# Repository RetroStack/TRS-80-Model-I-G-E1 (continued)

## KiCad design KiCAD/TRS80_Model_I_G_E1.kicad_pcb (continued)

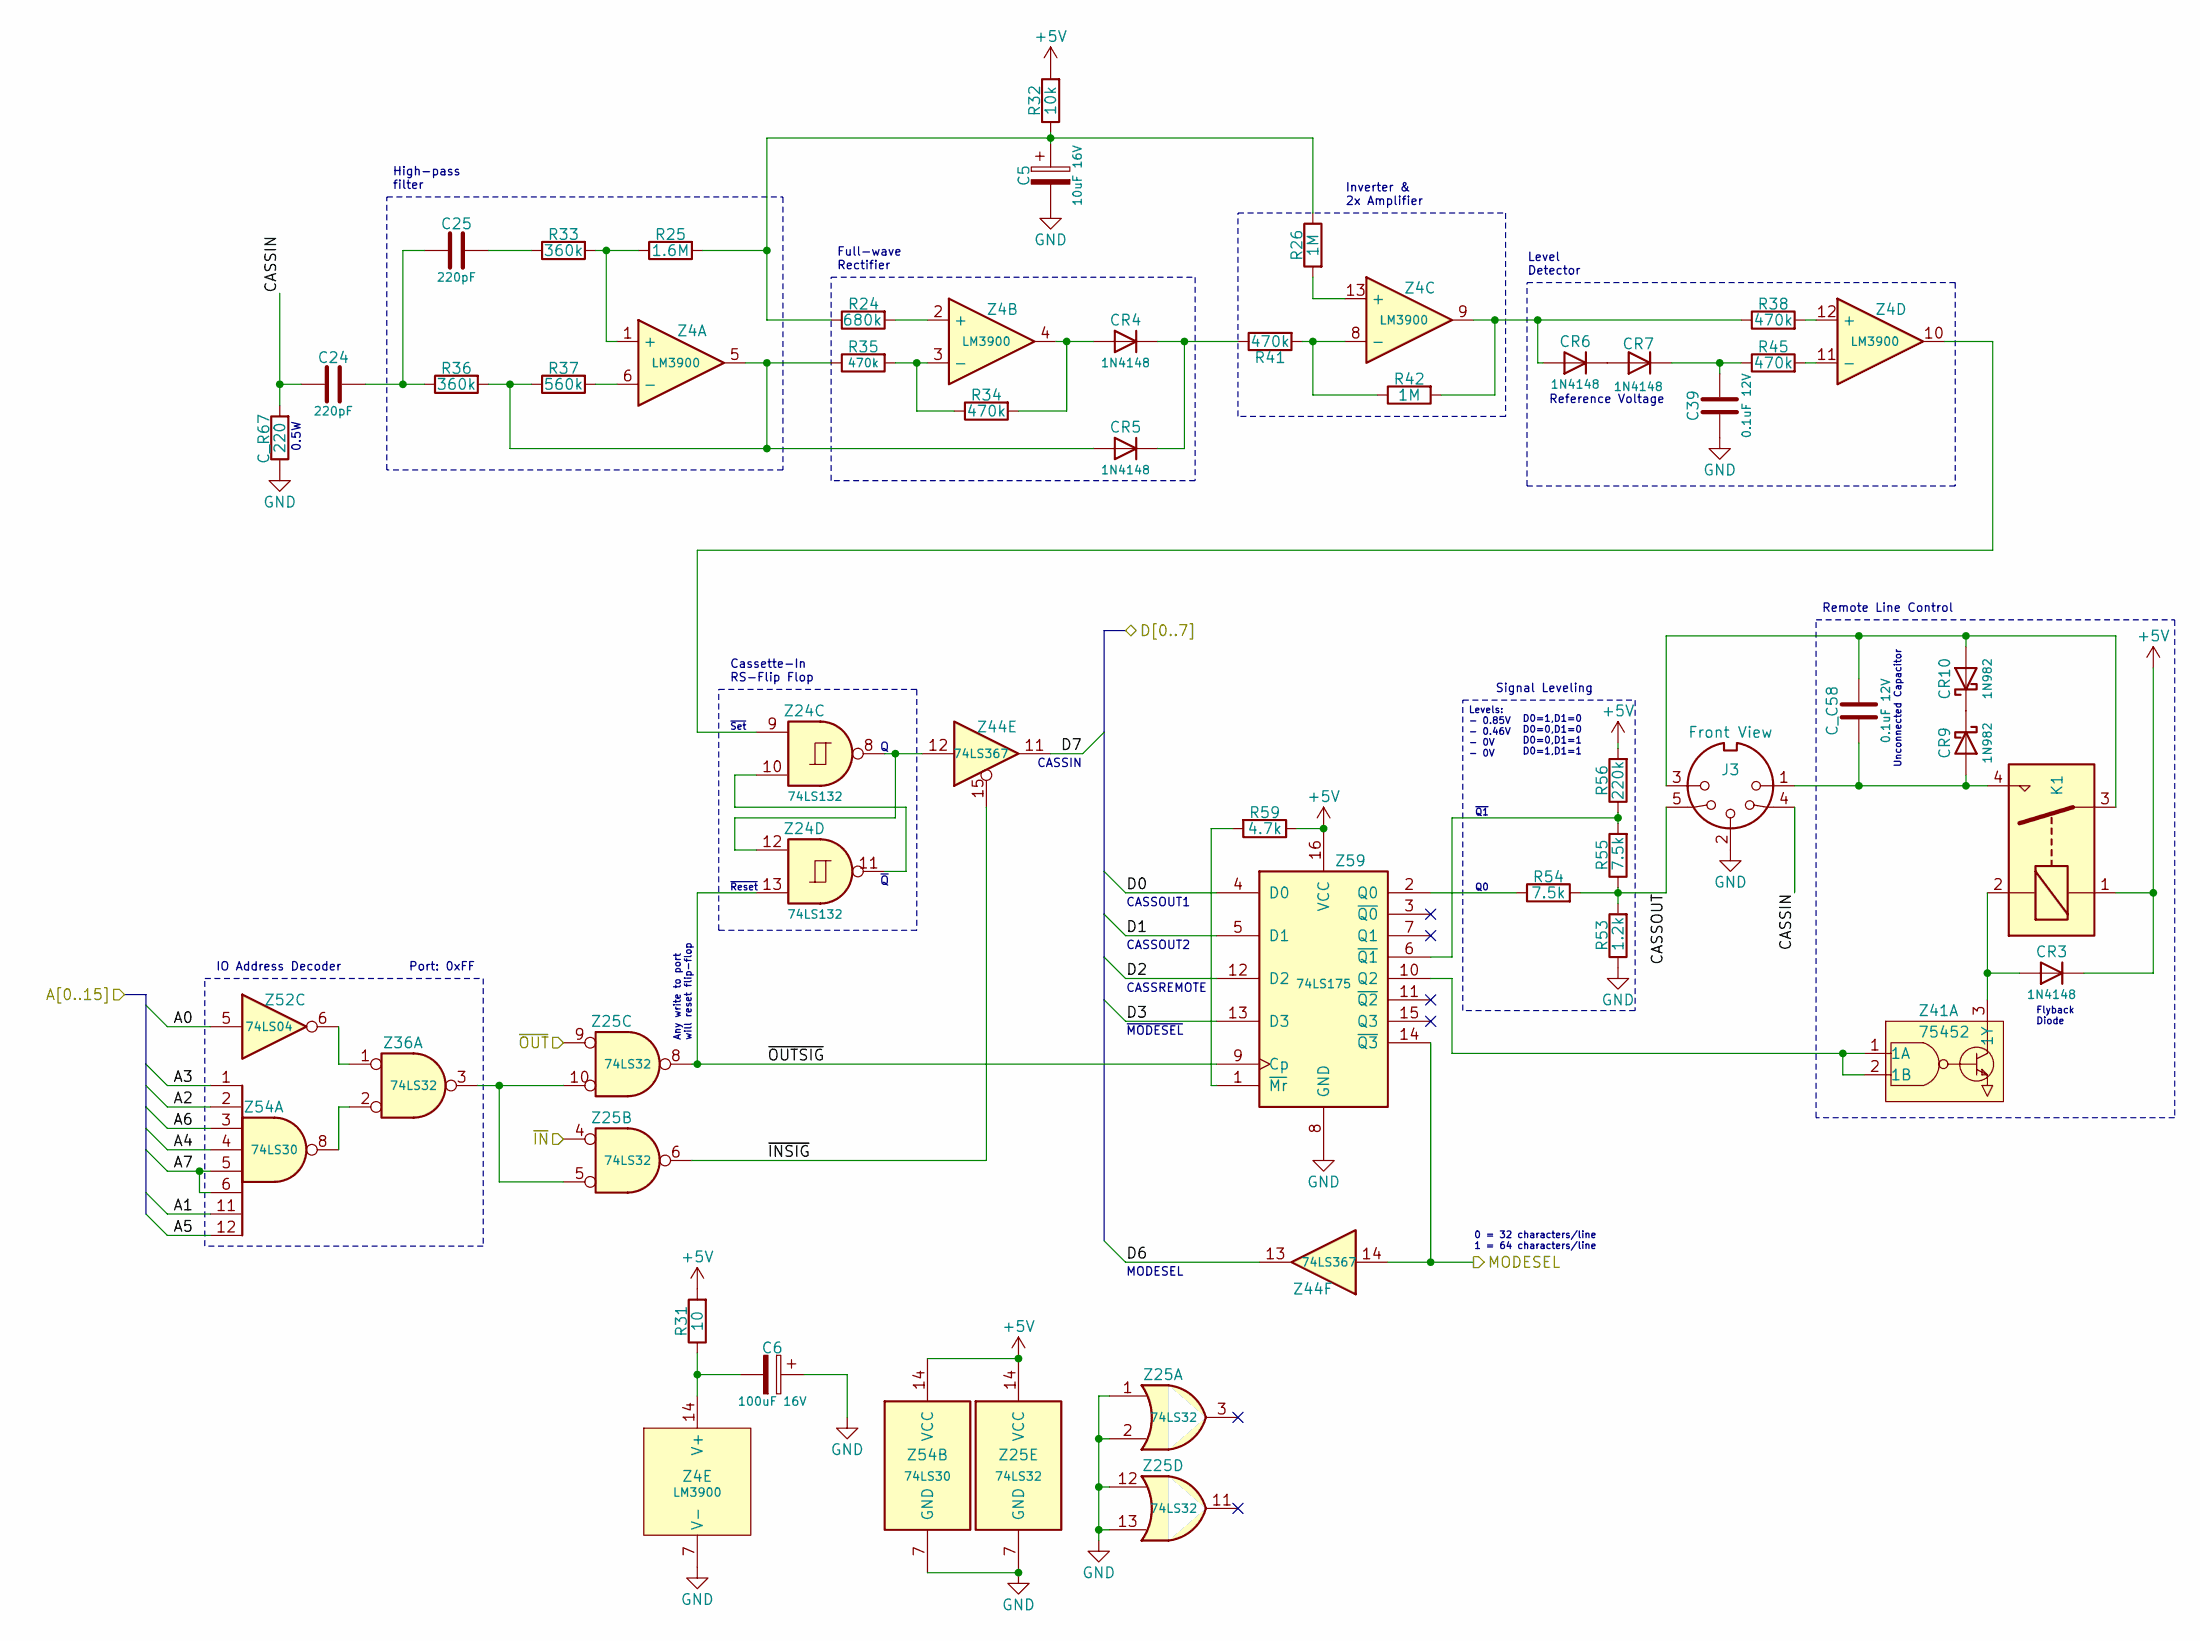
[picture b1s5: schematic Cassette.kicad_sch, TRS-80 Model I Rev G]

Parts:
C5: 10uF 16V; TRS80_Model_I_C_Pol_Radial_5D_2.5P
C6: 100uF 16V; TRS80_Model_I_C_Pol_Radial_10D_5P
C24, C25: 220pF; TRS80_Model_I_C_Disc_9.5L_4W_6P_Small
C39: 0.1uF 12V; TRS80_Model_I_C_Disc_9.5L_4W_6P_Small
CR3, CR4, CR5, CR6, CR7: 1N4148; TRS80_Model_I_D
CR9, CR10: 1N982; TRS80_Model_I_D
C_C58: 0.1uF 12V; TRS80_Model_I_C_Disc_9.5L_4W_6P_Small
C_R67: 220; TRS80_Model_I_R_0.25W
J3: Front View; TRS80_Model_I_DIN5
K1: Relay_SPST-NO; TRS80_Model_I_Relay
R24: 680k; TRS80_Model_I_R_0.25W
R25: 1.6M; TRS80_Model_I_R_0.25W
R26, R42: 1M; TRS80_Model_I_R_0.25W
R31: 10; TRS80_Model_I_R_0.25W
R32: 10k; TRS80_Model_I_R_0.25W
R33, R36: 360k; TRS80_Model_I_R_0.25W
R34, R35, R38, R41, R45: 470k; TRS80_Model_I_R_0.25W
R37: 560k; TRS80_Model_I_R_0.25W
R53: 1.2k; TRS80_Model_I_R_0.25W
R54, R55: 7.5k; TRS80_Model_I_R_0.25W
R56: 220k; TRS80_Model_I_R_0.25W
R59: 4.7k; TRS80_Model_I_R_0.25W
Z4: LM3900; TRS80_Model_I_DIP14
Z24: 74LS132; TRS80_Model_I_DIP14
Z25, Z36: 74LS32; TRS80_Model_I_DIP14
Z41: 75452; TRS80_Model_I_DIP8
Z44: 74LS367; TRS80_Model_I_DIP16
Z52: 74LS04; TRS80_Model_I_DIP14
Z54: 74LS30; TRS80_Model_I_DIP14
Z59: 74LS175; TRS80_Model_I_DIP16

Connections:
+5V: CR3.1 (K), K1.1, R31.2, R32.2, R56.2, R59.1, Z25.14 (VCC), Z54.14 (VCC), Z59.16 (VCC); also elsewhere on the board
/A0: Z52.5; also elsewhere on the board
/A1: Z54.11; also elsewhere on the board
/A2: Z54.2; also elsewhere on the board
/A3: Z54.1; also elsewhere on the board
/A4: Z54.4; also elsewhere on the board
/A5: Z54.12; also elsewhere on the board
/A6: Z54.3; also elsewhere on the board
/A7: Z54.5, Z54.6; also elsewhere on the board
/CPU Gating/~IN: Z25.4; also elsewhere on the board
/CPU Gating/~OUT: Z25.9; also elsewhere on the board
/Cassette Interface/CASSIN: C24.1, C_R67.2, J3.4
/Cassette Interface/CASSOUT: J3.5, R53.2, R54.2, R55.1
/Cassette Interface/MODESEL: Z44.14, Z59.14 (~Q3); also elsewhere on the board
/Cassette Interface/~INSIG: Z25.6, Z44.15
/Cassette Interface/~OUTSIG: Z24.13, Z25.8, Z59.9 (Cp)
/D0: Z59.4 (D0); also elsewhere on the board
/D1: Z59.5 (D1); also elsewhere on the board
/D2: Z59.12 (D2); also elsewhere on the board
/D3: Z59.13 (D3); also elsewhere on the board
/D6: Z44.13; also elsewhere on the board
/D7: Z44.11; also elsewhere on the board
GND: C5.2, C6.1, C39.1, C_R67.1, J3.2, R53.1, Z4.7 (V-), Z25.1, Z25.2, Z25.7 (GND), Z25.12, Z25.13, Z54.7 (GND), Z59.8 (GND); also elsewhere on the board
unnamed: C5.1, R24.1, R25.2, R26.1, R32.1
unnamed: C24.2, C25.1, R36.1
unnamed: C25.2, R33.1
unnamed: CR3.2 (A), K1.2, Z41.3 (1Y)
unnamed: CR4.2 (A), R34.2, Z4.4
unnamed: CR4.1 (K), CR5.1 (K), R41.1
unnamed: CR5.2 (A), R35.1, R36.2, R37.1, Z4.5
unnamed: CR6.2 (A), R38.1, R42.2, Z4.9
unnamed: CR6.1 (K), CR7.2 (A)
unnamed: C39.2, CR7.1 (K), R45.1
unnamed: CR9.2 (A), C_C58.2, J3.1, K1.4
unnamed: CR10.2 (A), C_C58.1, J3.3, K1.3
unnamed: CR9.1 (K), CR10.1 (K)
unnamed: R25.1, R33.2, Z4.1 (+)
unnamed: R37.2, Z4.6 (-)
unnamed: R24.2, Z4.2 (+)
unnamed: R34.1, R35.2, Z4.3 (-)
unnamed: R26.2, Z4.13 (+)
unnamed: R41.2, R42.1, Z4.8 (-)
unnamed: R38.2, Z4.12 (+)
unnamed: R45.2, Z4.11 (-)
unnamed: C6.2, R31.1, Z4.14 (V+)
unnamed: Z4.10, Z24.9
unnamed: Z24.10, Z24.11
unnamed: Z24.8, Z24.12, Z44.12
unnamed: Z25.5, Z25.10, Z36.3
unnamed: Z36.1, Z52.6
unnamed: Z36.2, Z54.8
unnamed: Z41.1 (1A), Z41.2 (1B), Z59.10 (Q2)
unnamed: R54.1, Z59.2 (Q0)
unnamed: R59.2, Z59.1 (~Mr)
unnamed: R55.2, R56.1, Z59.6 (~Q1)

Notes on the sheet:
~{MODESEL}
0 = 32 characters/line 1 = 64 characters/line
Full-wave Rectifier
Level Detector
High-pass filter
Unconnected Capacitor
Reference Voltage
Any write to port will reset flip-flop
IO Address Decoder
CASSREMOTE
Remote Line Control
Port: 0xFF
~{Q}
CASSOUT1
Flyback Diode
Signal Leveling
0.5W
CASSOUT2
CASSIN
MODESEL
Cassette-In RS-Flip Flop
~{Q1}
Levels: - 0.85V - 0.46V - 0V - 0V
Inverter & 2x Amplifier
~{Reset}
~{Set}
D0=1,D1=0 D0=0,D1=0 D0=0,D1=1 D0=1,D1=1

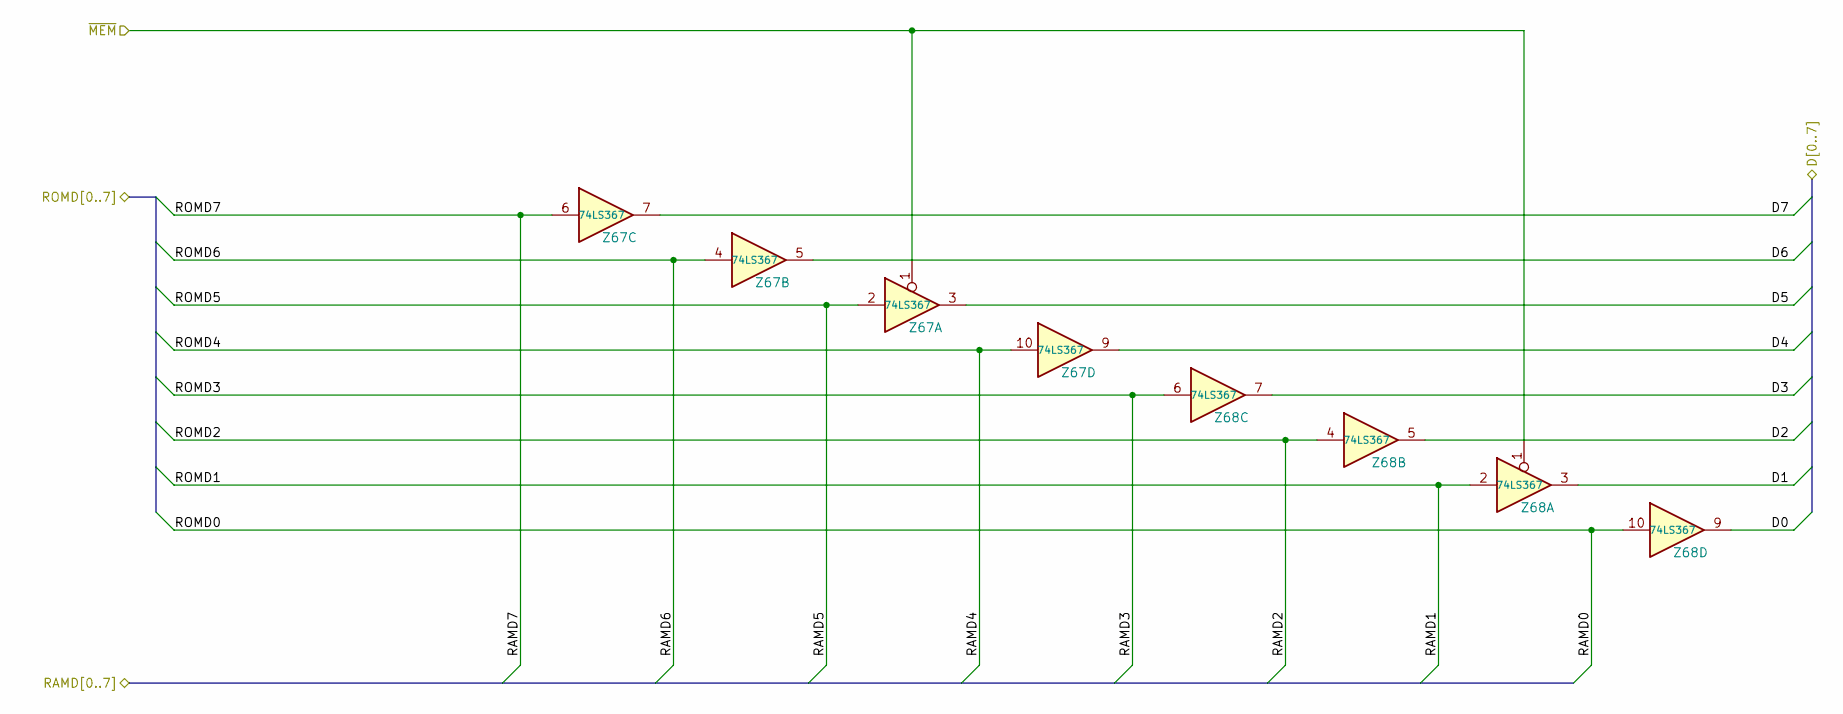
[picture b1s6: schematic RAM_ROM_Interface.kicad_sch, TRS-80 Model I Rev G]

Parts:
Z67, Z68: 74LS367; TRS80_Model_I_DIP16

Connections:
/Address Decoder/~MEM: Z67.1, Z68.1; also elsewhere on the board
/D0: Z68.9; also elsewhere on the board
/D1: Z68.3; also elsewhere on the board
/D2: Z68.5; also elsewhere on the board
/D3: Z68.7; also elsewhere on the board
/D4: Z67.9; also elsewhere on the board
/D5: Z67.3; also elsewhere on the board
/D6: Z67.5; also elsewhere on the board
/D7: Z67.7; also elsewhere on the board
/RAM-ROM Interface/ROMD0: Z68.10; also elsewhere on the board
/RAM-ROM Interface/ROMD1: Z68.2; also elsewhere on the board
/RAM-ROM Interface/ROMD2: Z68.4; also elsewhere on the board
/RAM-ROM Interface/ROMD3: Z68.6; also elsewhere on the board
/RAM-ROM Interface/ROMD4: Z67.10; also elsewhere on the board
/RAM-ROM Interface/ROMD5: Z67.2; also elsewhere on the board
/RAM-ROM Interface/ROMD6: Z67.4; also elsewhere on the board
/RAM-ROM Interface/ROMD7: Z67.6; also elsewhere on the board

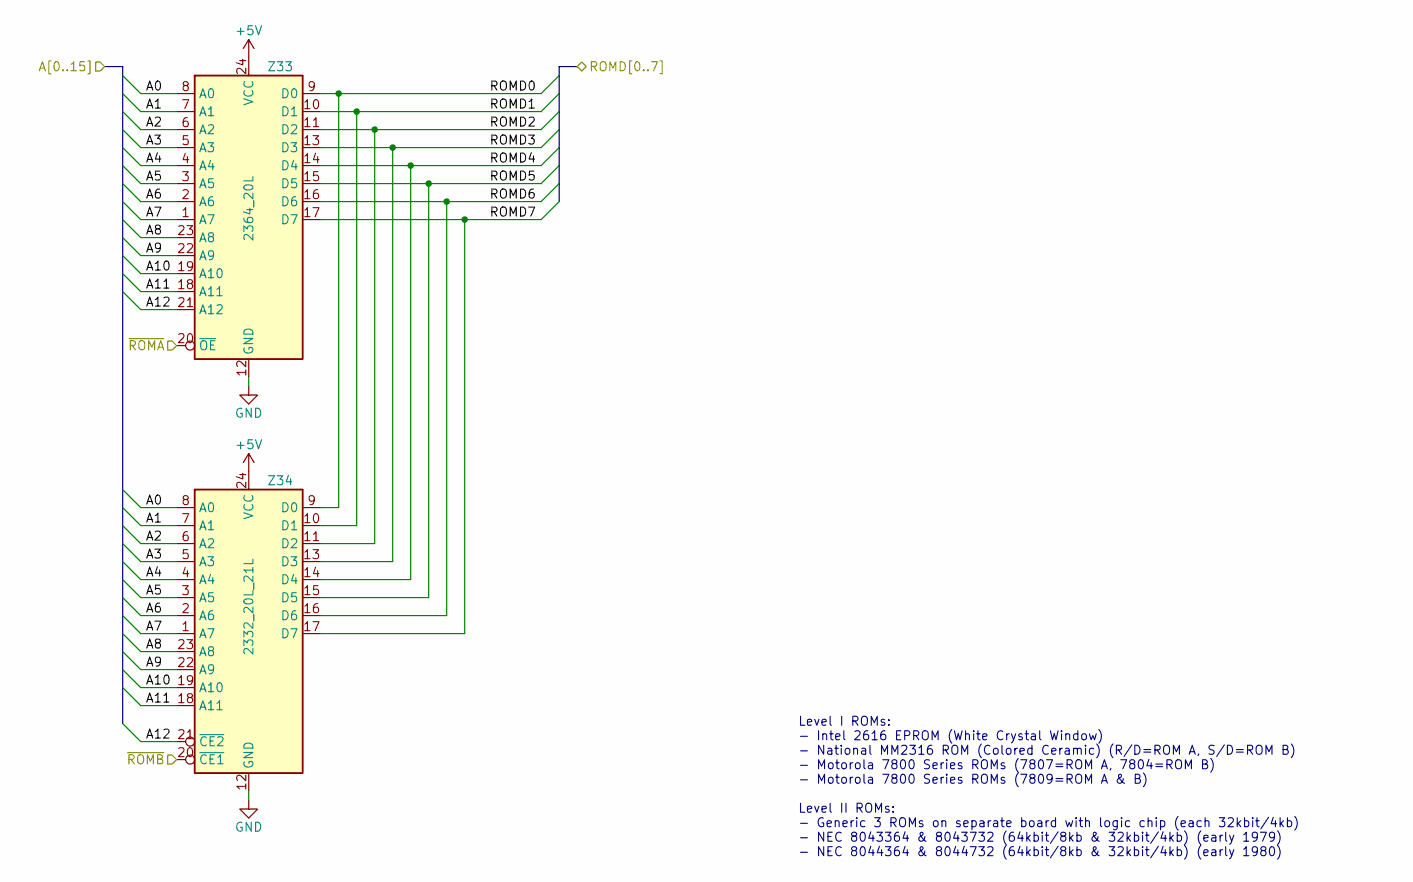
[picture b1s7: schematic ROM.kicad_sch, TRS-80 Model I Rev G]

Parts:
Z33: 2364_20L; DIP-24_W15.24mm
Z34: 2332_20L_21L; DIP-24_W15.24mm

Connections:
+5V: Z33.24 (VCC), Z34.24 (VCC); also elsewhere on the board
/A0: Z33.8 (A0), Z34.8 (A0); also elsewhere on the board
/A1: Z33.7 (A1), Z34.7 (A1); also elsewhere on the board
/A2: Z33.6 (A2), Z34.6 (A2); also elsewhere on the board
/A3: Z33.5 (A3), Z34.5 (A3); also elsewhere on the board
/A4: Z33.4 (A4), Z34.4 (A4); also elsewhere on the board
/A5: Z33.3 (A5), Z34.3 (A5); also elsewhere on the board
/A6: Z33.2 (A6), Z34.2 (A6); also elsewhere on the board
/A7: Z33.1 (A7), Z34.1 (A7); also elsewhere on the board
/A8: Z33.23 (A8), Z34.23 (A8); also elsewhere on the board
/A9: Z33.22 (A9), Z34.22 (A9); also elsewhere on the board
/A10: Z33.19 (A10), Z34.19 (A10); also elsewhere on the board
/A11: Z33.18 (A11), Z34.18 (A11); also elsewhere on the board
/A12: Z33.21 (A12), Z34.21 (~CE2); also elsewhere on the board
/Address Decoder/~ROMA: Z33.20 (~OE); also elsewhere on the board
/Address Decoder/~ROMB: Z34.20 (~CE1); also elsewhere on the board
/RAM-ROM Interface/ROMD0: Z33.9 (D0), Z34.9 (D0); also elsewhere on the board
/RAM-ROM Interface/ROMD1: Z33.10 (D1), Z34.10 (D1); also elsewhere on the board
/RAM-ROM Interface/ROMD2: Z33.11 (D2), Z34.11 (D2); also elsewhere on the board
/RAM-ROM Interface/ROMD3: Z33.13 (D3), Z34.13 (D3); also elsewhere on the board
/RAM-ROM Interface/ROMD4: Z33.14 (D4), Z34.14 (D4); also elsewhere on the board
/RAM-ROM Interface/ROMD5: Z33.15 (D5), Z34.15 (D5); also elsewhere on the board
/RAM-ROM Interface/ROMD6: Z33.16 (D6), Z34.16 (D6); also elsewhere on the board
/RAM-ROM Interface/ROMD7: Z33.17 (D7), Z34.17 (D7); also elsewhere on the board
GND: Z33.12 (GND), Z34.12 (GND); also elsewhere on the board

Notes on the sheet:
Level I ROMs: - Intel 2616 EPROM (White Crystal Window) - National MM2316 ROM (Colored Ceramic) (R/D=ROM A, S/D=ROM B) - Motorola 7800 Series ROMs (7807=ROM A, 7804=ROM B) - Motorola 7800 Series ROMs (7809=ROM A & B) Level II ROMs: - Generic 3 ROMs on separate board with logic chip (each 32kbit/4kb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

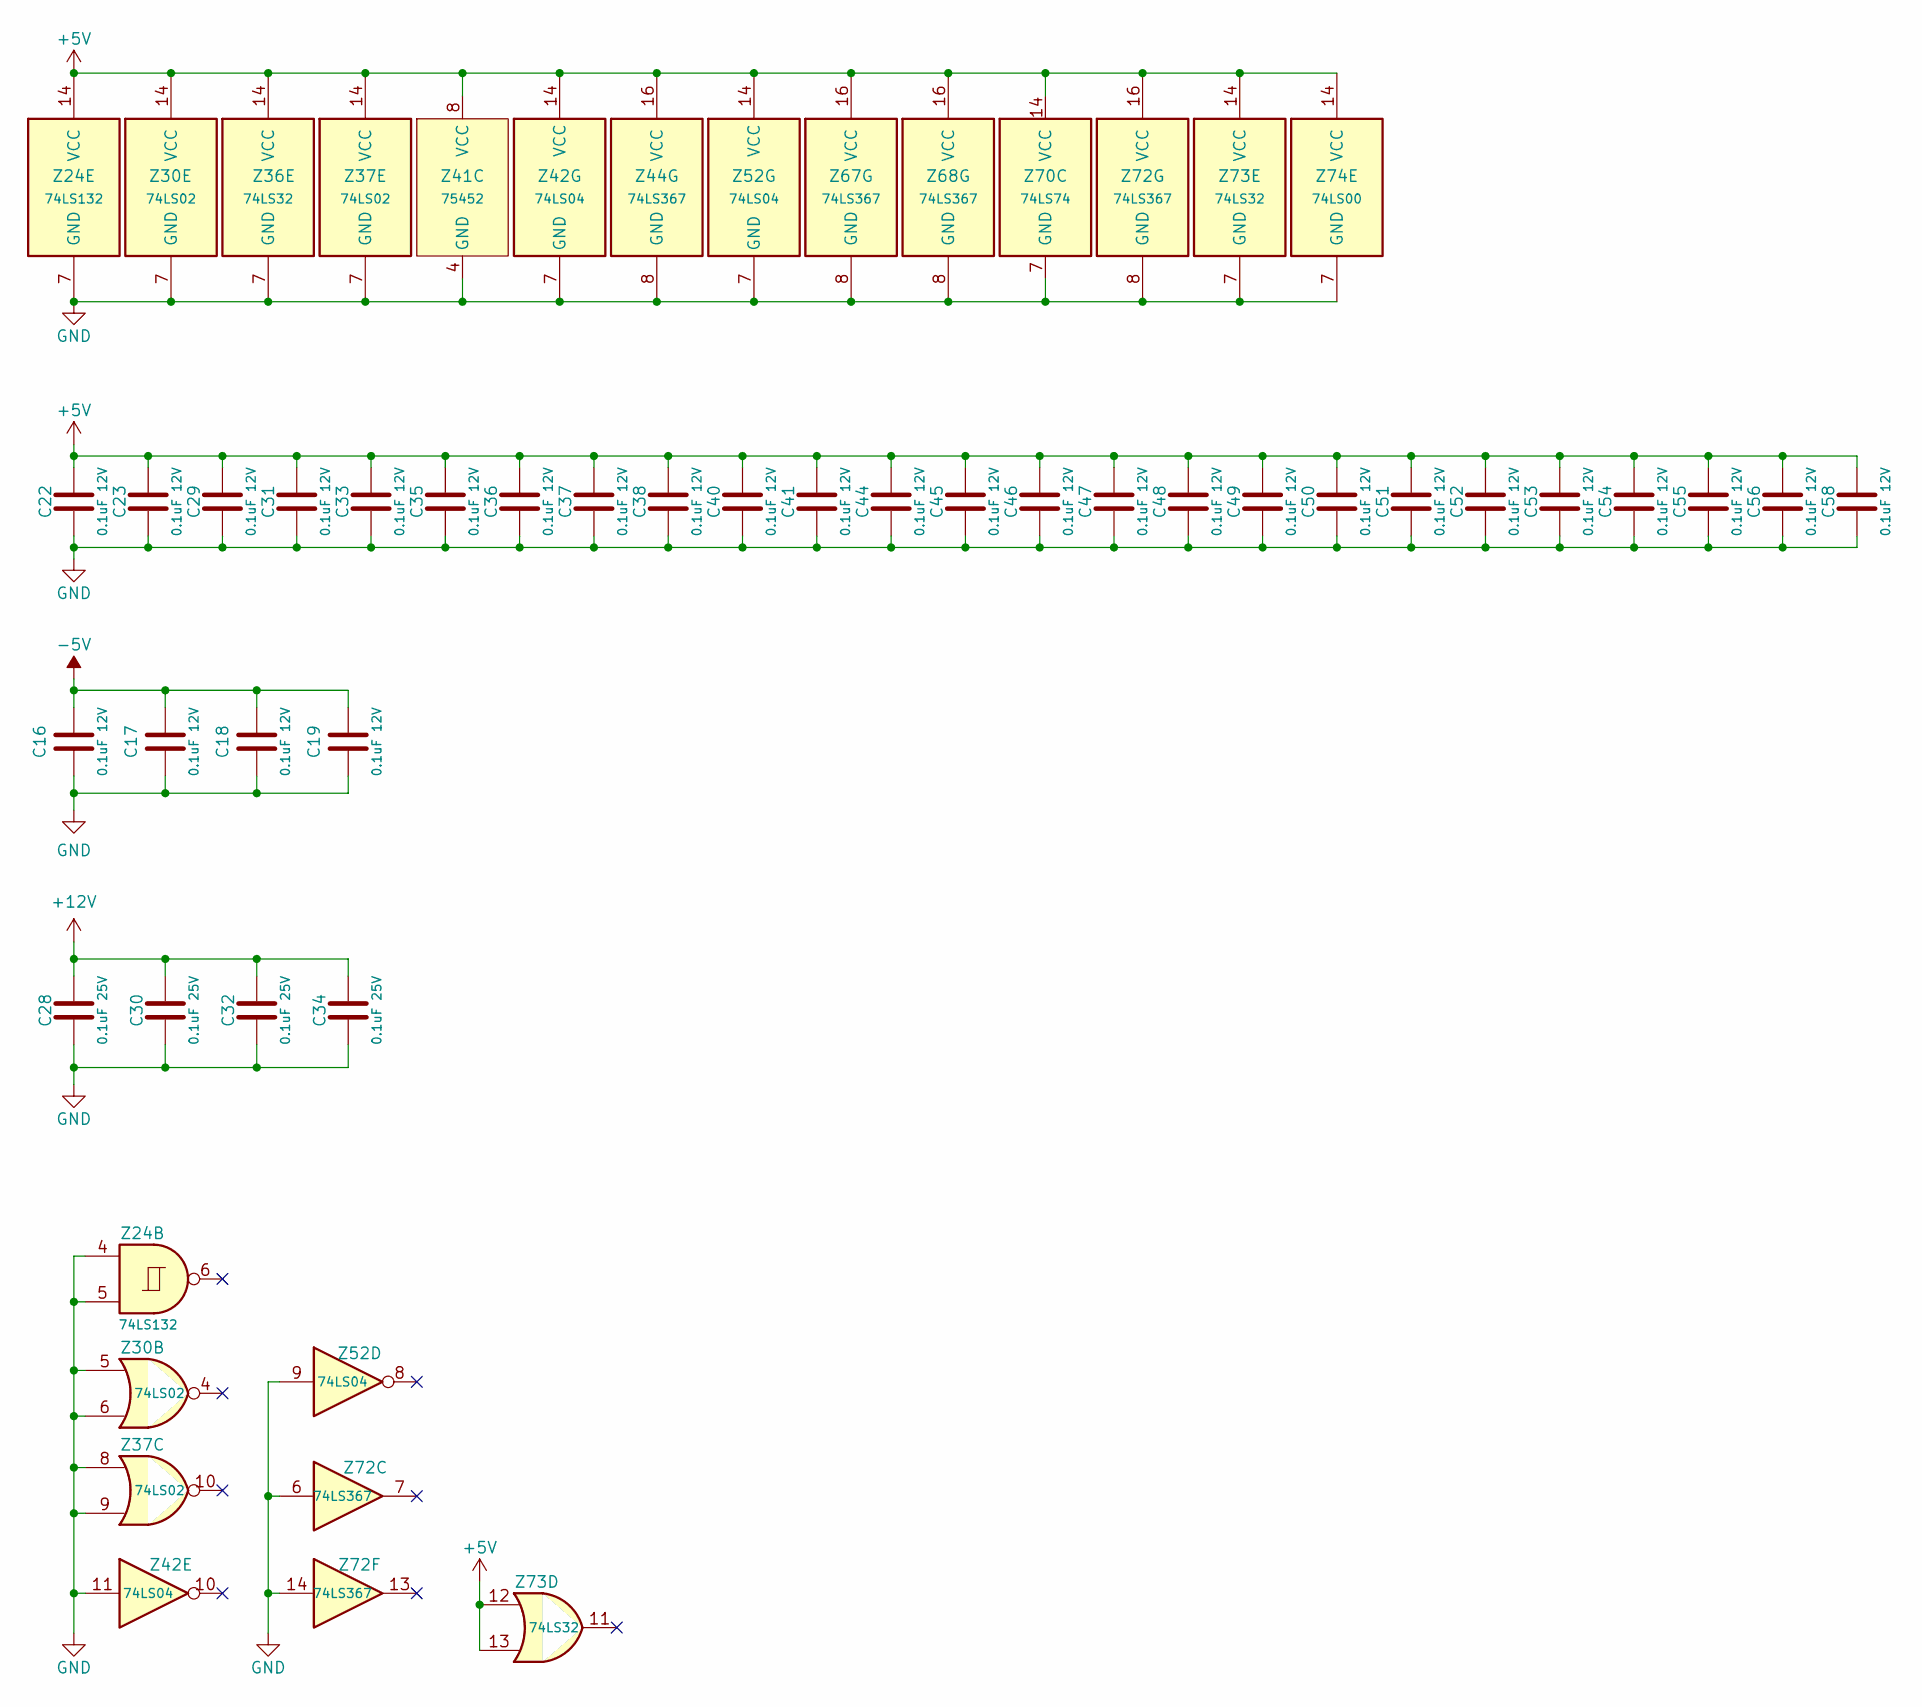
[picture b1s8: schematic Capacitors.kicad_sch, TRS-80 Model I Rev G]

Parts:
C16, C17, C18, C19, C22, C23, C29, C31, C33, C35, C36, C37, C38, C40, C41, C44, C45, C46, C47, C48, C49, C50, C51, C52, C53, C54, C55, C56, C58: 0.1uF 12V; TRS80_Model_I_C_Disc_9.5L_4W_6P_Small
C28, C30, C32, C34: 0.1uF 25V; TRS80_Model_I_C_Disc_18.5L_4W_8.5P_Large
Z24: 74LS132; TRS80_Model_I_DIP14
Z30, Z37: 74LS02; TRS80_Model_I_DIP14
Z36, Z73: 74LS32; TRS80_Model_I_DIP14
Z41: 75452; TRS80_Model_I_DIP8
Z42, Z52: 74LS04; TRS80_Model_I_DIP14
Z44, Z67, Z68, Z72: 74LS367; TRS80_Model_I_DIP16
Z70: 74LS74; TRS80_Model_I_DIP14
Z74: 74LS00; TRS80_Model_I_DIP14

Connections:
+5V: C22.1, C23.1, C29.1, C31.1, C33.1, C35.1, C36.1, C37.1, C38.1, C40.1, C41.1, C44.1, C45.1, C46.1, C47.1, C48.1, C49.1, C50.1, C51.1, C52.1, C53.1, C54.1, C55.1, C56.1, C58.1, Z24.14 (VCC), Z30.14 (VCC), Z36.14 (VCC), Z37.14 (VCC), Z41.8 (VCC), Z42.14 (VCC), Z44.16 (VCC), Z52.14 (VCC), Z67.16 (VCC), Z68.16 (VCC), Z70.14 (VCC), Z72.16 (VCC), Z73.12, Z73.13, Z73.14 (VCC), Z74.14 (VCC); also elsewhere on the board
+12V: C28.1, C30.1, C32.1, C34.1; also elsewhere on the board
-5V: C16.1, C17.1, C18.1, C19.1; also elsewhere on the board
/Cassette Interface/MODESEL: Z44.14; also elsewhere on the board
/D6: Z44.13; also elsewhere on the board
GND: C16.2, C17.2, C18.2, C19.2, C22.2, C23.2, C28.2, C29.2, C30.2, C31.2, C32.2, C33.2, C34.2, C35.2, C36.2, C37.2, C38.2, C40.2, C41.2, C44.2, C45.2, C46.2, C47.2, C48.2, C49.2, C50.2, C51.2, C52.2, C53.2, C54.2, C55.2, C56.2, C58.2, Z24.4, Z24.5, Z24.7 (GND), Z30.5, Z30.6, Z30.7 (GND), Z36.7 (GND), Z37.7 (GND), Z37.8, Z37.9, Z41.4 (GND), Z42.7 (GND), Z42.11, Z44.8 (GND), Z52.7 (GND), Z52.9, Z67.8 (GND), Z68.8 (GND), Z70.7 (GND), Z72.6, Z72.8 (GND), Z72.14, Z73.7 (GND), Z74.7 (GND); also elsewhere on the board

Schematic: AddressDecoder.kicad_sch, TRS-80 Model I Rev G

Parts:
R48, R61, R62, R68: 4.7k; TRS80_Model_I_R_0.25W
Z3: DIP-16_W7.62mm
Z21: 74LS156; TRS80_Model_I_DIP16
Z36, Z73: 74LS32; TRS80_Model_I_DIP14
Z37: 74LS02; TRS80_Model_I_DIP14
Z52: 74LS04; TRS80_Model_I_DIP14
Z74: 74LS00; TRS80_Model_I_DIP14

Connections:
+5V: R48.2, R61.2, R62.2, R68.2, Z21.16 (VCC); also elsewhere on the board
/A10: Z36.13, Z52.1; also elsewhere on the board
/A11: Z37.5, Z37.6; also elsewhere on the board
/A12: Z21.13 (A0); also elsewhere on the board
/A13: Z21.3 (A1); also elsewhere on the board
/A14: Z21.1 (Ea1), Z21.15 (Eb2); also elsewhere on the board
/A15: Z73.4; also elsewhere on the board
/Address Decoder/~KYBD: Z36.11; also elsewhere on the board
/Address Decoder/~MEM: Z74.6; also elsewhere on the board
/Address Decoder/~RAM: R62.1, Z3.12, Z3.13, Z3.14, Z3.15, Z74.10; also elsewhere on the board
/Address Decoder/~RAS: Z73.5; also elsewhere on the board
/Address Decoder/~RD: Z52.13; also elsewhere on the board
/Address Decoder/~ROMA: R61.1, Z3.7, Z3.8, Z74.9; also elsewhere on the board
/Address Decoder/~ROMB: R68.1, Z3.1, Z3.6, Z74.12, Z74.13; also elsewhere on the board
/Address Decoder/~VID: Z36.8; also elsewhere on the board
GND: Z21.8 (GND); also elsewhere on the board
unnamed: Z21.2 (Ea2), Z21.14 (Eb1), Z73.6
unnamed: Z3.2, Z21.7 (Q0a)
unnamed: Z3.10, Z3.16, Z21.9 (Q0b)
unnamed: Z3.3, Z21.6 (Q1a)
unnamed: Z3.9, Z21.10 (Q1b)
unnamed: Z3.4, Z21.5 (Q2a)
unnamed: Z3.11, Z21.11 (Q2b)
unnamed: Z3.5, Z21.4 (Q3a)
unnamed: R48.1, Z21.12 (Q3b), Z36.4
unnamed: Z36.5, Z37.4
unnamed: Z36.9, Z52.2
unnamed: Z36.6, Z36.10, Z36.12
unnamed: Z52.12, Z74.4
unnamed: Z73.8, Z74.5
unnamed: Z73.9, Z74.8
unnamed: Z73.10, Z74.11

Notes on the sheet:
38xx..3Bxx
5xxx
4xxx
0001
0000
0111
RAS=0 && A15=0
7xxx
0xxx, 2xxx
2xxx
0100
0xxx, 1xxx
0011
4xxx..7xxx
0010
0101
3Cxx..3Fxx
0xxx
A14=0
A14=1
0110
6xxx
1xxx
3xxx

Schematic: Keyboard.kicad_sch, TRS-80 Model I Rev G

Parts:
J100: Connection Mainboard Side; TRS80_Model_I_Keyboard_Connector

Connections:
+5V: J100.1; also elsewhere on the board
/A0: J100.5; also elsewhere on the board
/A1: J100.4; also elsewhere on the board
/A2: J100.6; also elsewhere on the board
/A3: J100.9; also elsewhere on the board
/A4: J100.2; also elsewhere on the board
/A5: J100.3; also elsewhere on the board
/A6: J100.7; also elsewhere on the board
/A7: J100.8; also elsewhere on the board
/Address Decoder/~KYBD: J100.14; also elsewhere on the board
/D0: J100.11; also elsewhere on the board
/D1: J100.16; also elsewhere on the board
/D2: J100.10; also elsewhere on the board
/D3: J100.13; also elsewhere on the board
/D4: J100.18; also elsewhere on the board
/D5: J100.12; also elsewhere on the board
/D6: J100.15; also elsewhere on the board
/D7: J100.17; also elsewhere on the board
GND: J100.19; also elsewhere on the board

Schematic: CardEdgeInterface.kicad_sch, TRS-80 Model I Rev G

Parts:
J4: Edge Connector; TRS80_Model_I_Edge_Connector
R50, R51, R58: 4.7k; TRS80_Model_I_R_0.25W

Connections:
+5V: R50.1, R51.1, R58.1; also elsewhere on the board
/A0: J4.25; also elsewhere on the board
/A1: J4.27; also elsewhere on the board
/A2: J4.40; also elsewhere on the board
/A3: J4.34; also elsewhere on the board
/A4: J4.31; also elsewhere on the board
/A5: J4.35; also elsewhere on the board
/A6: J4.38; also elsewhere on the board
/A7: J4.36; also elsewhere on the board
/A8: J4.11; also elsewhere on the board
/A9: J4.17; also elsewhere on the board
/A10: J4.4; also elsewhere on the board
/A11: J4.9; also elsewhere on the board
/A12: J4.5; also elsewhere on the board
/A13: J4.6; also elsewhere on the board
/A14: J4.10; also elsewhere on the board
/A15: J4.7; also elsewhere on the board
/Address Decoder/~RAS: J4.1; also elsewhere on the board
/Address Decoder/~RD: J4.15; also elsewhere on the board
/CPU Gating/MUX: J4.16; also elsewhere on the board
/CPU Gating/~CAS: J4.3; also elsewhere on the board
/CPU Gating/~IN: J4.19; also elsewhere on the board
/CPU Gating/~OUT: J4.12; also elsewhere on the board
/CPU Gating/~TEST: J4.23, R58.2; also elsewhere on the board
/CPU Gating/~WR: J4.13; also elsewhere on the board
/CPU/~INTAK: J4.14; also elsewhere on the board
/CPU/~INT: J4.21, R50.2; also elsewhere on the board
/CPU/~SYSRES: J4.2; also elsewhere on the board
/CPU/~WAIT: J4.33, R51.2; also elsewhere on the board
/D0: J4.30; also elsewhere on the board
/D1: J4.22; also elsewhere on the board
/D2: J4.32; also elsewhere on the board
/D3: J4.26; also elsewhere on the board
/D4: J4.18; also elsewhere on the board
/D5: J4.28; also elsewhere on the board
/D6: J4.24; also elsewhere on the board
/D7: J4.20; also elsewhere on the board
GND: J4.8, J4.29, J4.37, J4.39; also elsewhere on the board

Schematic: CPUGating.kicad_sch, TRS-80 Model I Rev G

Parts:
Z22, Z38, Z39, Z55, Z72, Z75, Z76: 74LS367; TRS80_Model_I_DIP16
Z52: 74LS04; TRS80_Model_I_DIP14

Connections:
+5V: Z22.16 (VCC), Z38.16 (VCC), Z39.16 (VCC), Z55.16 (VCC), Z75.16 (VCC), Z76.16 (VCC); also elsewhere on the board
/A0: Z55.11; also elsewhere on the board
/A1: Z55.13; also elsewhere on the board
/A2: Z22.11; also elsewhere on the board
/A3: Z22.13; also elsewhere on the board
/A4: Z39.7; also elsewhere on the board
/A5: Z39.9; also elsewhere on the board
/A6: Z39.5; also elsewhere on the board
/A7: Z39.11; also elsewhere on the board
/A8: Z39.3; also elsewhere on the board
/A9: Z39.13; also elsewhere on the board
/A10: Z38.3; also elsewhere on the board
/A11: Z38.13; also elsewhere on the board
/A12: Z38.5; also elsewhere on the board
/A13: Z38.7; also elsewhere on the board
/A14: Z38.11; also elsewhere on the board
/A15: Z38.9; also elsewhere on the board
/Address Decoder/~RAS: Z72.5; also elsewhere on the board
/Address Decoder/~RD: Z22.7; also elsewhere on the board
/CPU Gating/MUX: Z72.3; also elsewhere on the board
/CPU Gating/ZA0: Z55.12; also elsewhere on the board
/CPU Gating/ZA1: Z55.14; also elsewhere on the board
/CPU Gating/ZA2: Z22.12; also elsewhere on the board
/CPU Gating/ZA3: Z22.14; also elsewhere on the board
/CPU Gating/ZA4: Z39.6; also elsewhere on the board
/CPU Gating/ZA5: Z39.10; also elsewhere on the board
/CPU Gating/ZA6: Z39.4; also elsewhere on the board
/CPU Gating/ZA7: Z39.12; also elsewhere on the board
/CPU Gating/ZA8: Z39.2; also elsewhere on the board
/CPU Gating/ZA9: Z39.14; also elsewhere on the board
/CPU Gating/ZA10: Z38.2; also elsewhere on the board
/CPU Gating/ZA11: Z38.14; also elsewhere on the board
/CPU Gating/ZA12: Z38.4; also elsewhere on the board
/CPU Gating/ZA13: Z38.6; also elsewhere on the board
/CPU Gating/ZA14: Z38.12; also elsewhere on the board
/CPU Gating/ZA15: Z38.10; also elsewhere on the board
/CPU Gating/ZD0: Z76.9, Z76.12; also elsewhere on the board
/CPU Gating/ZD1: Z76.3, Z76.14; also elsewhere on the board
/CPU Gating/ZD2: Z75.14, Z76.5; also elsewhere on the board
/CPU Gating/ZD3: Z55.5, Z75.4; also elsewhere on the board
/CPU Gating/ZD4: Z55.3, Z75.6; also elsewhere on the board
/CPU Gating/ZD5: Z55.7, Z75.2; also elsewhere on the board
/CPU Gating/ZD6: Z55.9, Z75.10; also elsewhere on the board
/CPU Gating/ZD7: Z75.12, Z76.7; also elsewhere on the board
/CPU Gating/ZMUX: Z72.2; also elsewhere on the board
/CPU Gating/~CAS: Z72.9; also elsewhere on the board
/CPU Gating/~DBIN: Z55.1, Z76.1; also elsewhere on the board
/CPU Gating/~DBOUT: Z75.1, Z75.15, Z76.15; also elsewhere on the board
/CPU Gating/~IN: Z22.9; also elsewhere on the board
/CPU Gating/~OUT: Z22.3; also elsewhere on the board
/CPU Gating/~TEST: Z52.3; also elsewhere on the board
/CPU Gating/~WR: Z22.5; also elsewhere on the board
/CPU Gating/~ZCAS: Z72.10; also elsewhere on the board
/CPU Gating/~ZIN: Z22.10; also elsewhere on the board
/CPU Gating/~ZOUT: Z22.2; also elsewhere on the board
/CPU Gating/~ZRAS: Z72.4; also elsewhere on the board
/CPU Gating/~ZRD: Z22.6; also elsewhere on the board
/CPU Gating/~ZWR: Z22.4; also elsewhere on the board
/D0: Z76.10, Z76.11; also elsewhere on the board
/D1: Z76.2, Z76.13; also elsewhere on the board
/D2: Z75.13, Z76.4; also elsewhere on the board
/D3: Z55.4, Z75.5; also elsewhere on the board
/D4: Z55.2, Z75.7; also elsewhere on the board
/D5: Z55.6, Z75.3; also elsewhere on the board
/D6: Z55.10, Z75.9; also elsewhere on the board
/D7: Z75.11, Z76.6; also elsewhere on the board
GND: Z22.8 (GND), Z38.8 (GND), Z39.8 (GND), Z55.8 (GND), Z75.8 (GND), Z76.8 (GND); also elsewhere on the board
unnamed: Z22.1, Z22.15, Z38.1, Z38.15, Z39.1, Z39.15, Z52.4, Z55.15, Z72.1

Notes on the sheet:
Bi-directional Data Bus
Address Bus
Control Signals

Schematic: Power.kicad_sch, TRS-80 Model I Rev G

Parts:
C1: 220uF 16V; TRS80_Model_I_C_Pol_Axial_21L_9W_29P
C3, C14, C15: 0.01uF 24V; TRS80_Model_I_C_Disc_9.5L_4W_6P_Small
C4, C10, C11: 10uF 16V; TRS80_Model_I_C_Pol_Radial_5D_2.5P
C8: 2200uF 35V; TRS80_Model_I_C_Pol_Axial_41L_19W_48P
C9: 10000uF 16V; TRS80_Model_I_C_Pol_Axial_63L_25W_71P
C12, C13: 470pF; TRS80_Model_I_C_Disc_9.5L_4W_6P_Small
CR1: 1N4735; TRS80_Model_I_D
CR2: 1N5231; TRS80_Model_I_D
CR8: MDA202; TRS80_Model_I_D_Bridge
J1: Front View; TRS80_Model_I_DIN5
Q3: TIP29A; TRS80_Model_I_Q_Box_BCE
Q4: 2N6594; TRS80_Model_I_Q_Heatsink_Large_BEC
Q5: 2N3906; TRS80_Model_I_Q_Circle_EBC
Q6: MJE34; TRS80_Model_I_Q_Heatsink_Small_BCE
R1: 68; TRS80_Model_I_R_0.25W
R2: 2.7k; TRS80_Model_I_R_0.25W
R3: 750; TRS80_Model_I_R_0.25W
R4: 0.33; TRS80_Model_I_R_2W
R5, R10: 1k; TRS80_Model_I_R_Pot
R6, R7, R16: 1.2k; TRS80_Model_I_R_0.25W
R8: 100k; TRS80_Model_I_R_0.25W
R9, R11, R12: 3.3k; TRS80_Model_I_R_0.25W
R13: 2.2k; TRS80_Model_I_R_0.25W
R14: 12k; TRS80_Model_I_R_0.25W
R15: 1.5k; TRS80_Model_I_R_0.25W
R17: 2k; TRS80_Model_I_R_0.25W
R18: 5.6; TRS80_Model_I_R_3W
R19: 220; TRS80_Model_I_R_0.5W
S1: TRS80_Model_I_Sw_Large
Z1, Z2: LM723C; TRS80_Model_I_DIP14

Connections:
+5V: C10.1, C14.1, CR1.1 (K), R4.2, R7.1, R8.2, Z1.3 (CSEN); also elsewhere on the board
+12V: C11.1, C15.1, R13.1, R18.1, Z1.11 (VC), Z1.12 (V+), Z2.3 (CSEN); also elsewhere on the board
-5V: C3.1, C4.2, CR2.2 (A), R19.1; also elsewhere on the board
GND: C1.1, C3.2, C4.1, C8.2, C9.2, C10.2, C11.2, C14.2, C15.2, CR1.2 (A), CR2.1 (K), J1.4, R11.2, R12.2, R14.2, Z1.7 (V-), Z2.7 (V-); also elsewhere on the board
unnamed: C1.2, R19.2, S1.10
unnamed: CR8.1 (+), S1.4, S1.5, S1.8, S1.9
unnamed: CR8.4 (-), S1.11, S1.12
unnamed: CR8.2, J1.1
unnamed: CR8.3, J1.3
unnamed: J1.2, S1.1, S1.2
unnamed: Q3.1 (B), R2.1, Z1.10 (Vout)
unnamed: Q3.2 (C), Q4.1 (B), R1.2
unnamed: Q3.3 (E), Q4.3 (C), R2.2, R3.1, R4.1
unnamed: C9.1, Q4.2 (E), R1.1, S1.6, S1.7
unnamed: Q5.2 (B), R8.1
unnamed: Q5.3 (C), R9.2
unnamed: Q5.1 (E), R5.2, Z1.5 (+)
unnamed: Q6.1 (B), R16.2, Z2.11 (VC)
unnamed: Q6.2 (C), R17.1, R18.2, Z2.10 (Vout)
unnamed: C8.1, Q6.3 (E), R16.1, S1.3, Z2.12 (V+)
unnamed: R5.1, R6.1
unnamed: R10.1, R12.1
unnamed: R10.3, R13.2
unnamed: R5.3, R11.1
unnamed: C12.1, R7.2, Z1.4 (-)
unnamed: C12.2, Z1.13 (FC)
unnamed: R3.2, R9.1, Z1.2 (ILIM)
unnamed: R6.2, Z1.6 (VREF)
unnamed: R15.2, Z2.5 (+)
unnamed: C13.2, R10.2, Z2.4 (-)
unnamed: C13.1, Z2.13 (FC)
unnamed: R14.1, R17.2, Z2.2 (ILIM)
unnamed: R15.1, Z2.6 (VREF)

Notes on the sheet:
12V-20V AC 1A
0.5W
14V-20V DC 350mA

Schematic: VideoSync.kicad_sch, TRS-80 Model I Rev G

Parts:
C20: 330pF; TRS80_Model_I_C_Disc_9.5L_4W_6P_Small
C21: 750pF; TRS80_Model_I_C_Disc_9.5L_4W_6P_Small
C26: 0.047uF; TRS80_Model_I_C_Box_11L_5W_6P_Large
C27: 0.022uF; TRS80_Model_I_C_Box_7.5L_5W_4.5P_Small
R20, R21: 100k; TRS80_Model_I_R_Pot
R43, R44: 10k; TRS80_Model_I_R_0.25W
Z5: 74C00; TRS80_Model_I_DIP14
Z6, Z57: 74C04; TRS80_Model_I_DIP14

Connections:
+5V: Z5.14 (VCC), Z6.14 (VCC), Z57.14 (VCC); also elsewhere on the board
/Video/Video Counter/HDRV: Z6.13; also elsewhere on the board
/Video/Video Counter/VDRV: Z57.1; also elsewhere on the board
/Video/Video Mixer/SYNC: Z5.8; also elsewhere on the board
GND: R43.2, R44.1, Z5.7 (GND), Z6.7 (GND), Z57.7 (GND); also elsewhere on the board
unnamed: C20.1, R20.2, Z6.3
unnamed: C20.2, C21.1, Z6.6
unnamed: C21.2, R43.1, Z6.11
unnamed: C26.1, R21.2, Z57.13
unnamed: C26.2, C27.1, Z57.10
unnamed: C27.2, R44.2, Z57.5
unnamed: R20.1, Z6.2
unnamed: R21.1, Z57.4
unnamed: Z5.1, Z5.5, Z57.8
unnamed: Z5.6, Z5.9
unnamed: Z5.10, Z5.11
unnamed: Z5.3, Z5.4, Z5.12
unnamed: Z5.2, Z5.13, Z6.8
unnamed: Z6.1, Z6.12
unnamed: Z6.4, Z6.5
unnamed: Z6.9, Z6.10
unnamed: Z57.2, Z57.3
unnamed: Z57.6, Z57.9
unnamed: Z57.11, Z57.12

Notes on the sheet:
Amplifier
Sync Offset
H-Sync
V-Sync Offset Capacitor
V-Sync
Inv-Sync
H-Sync Offset Capacitor
Sync Pulse Length
V-Sync Length
V-Sync Offset Resistor
H-Sync Length
Combine Sync Signals
H-Sync Offset Resistor
